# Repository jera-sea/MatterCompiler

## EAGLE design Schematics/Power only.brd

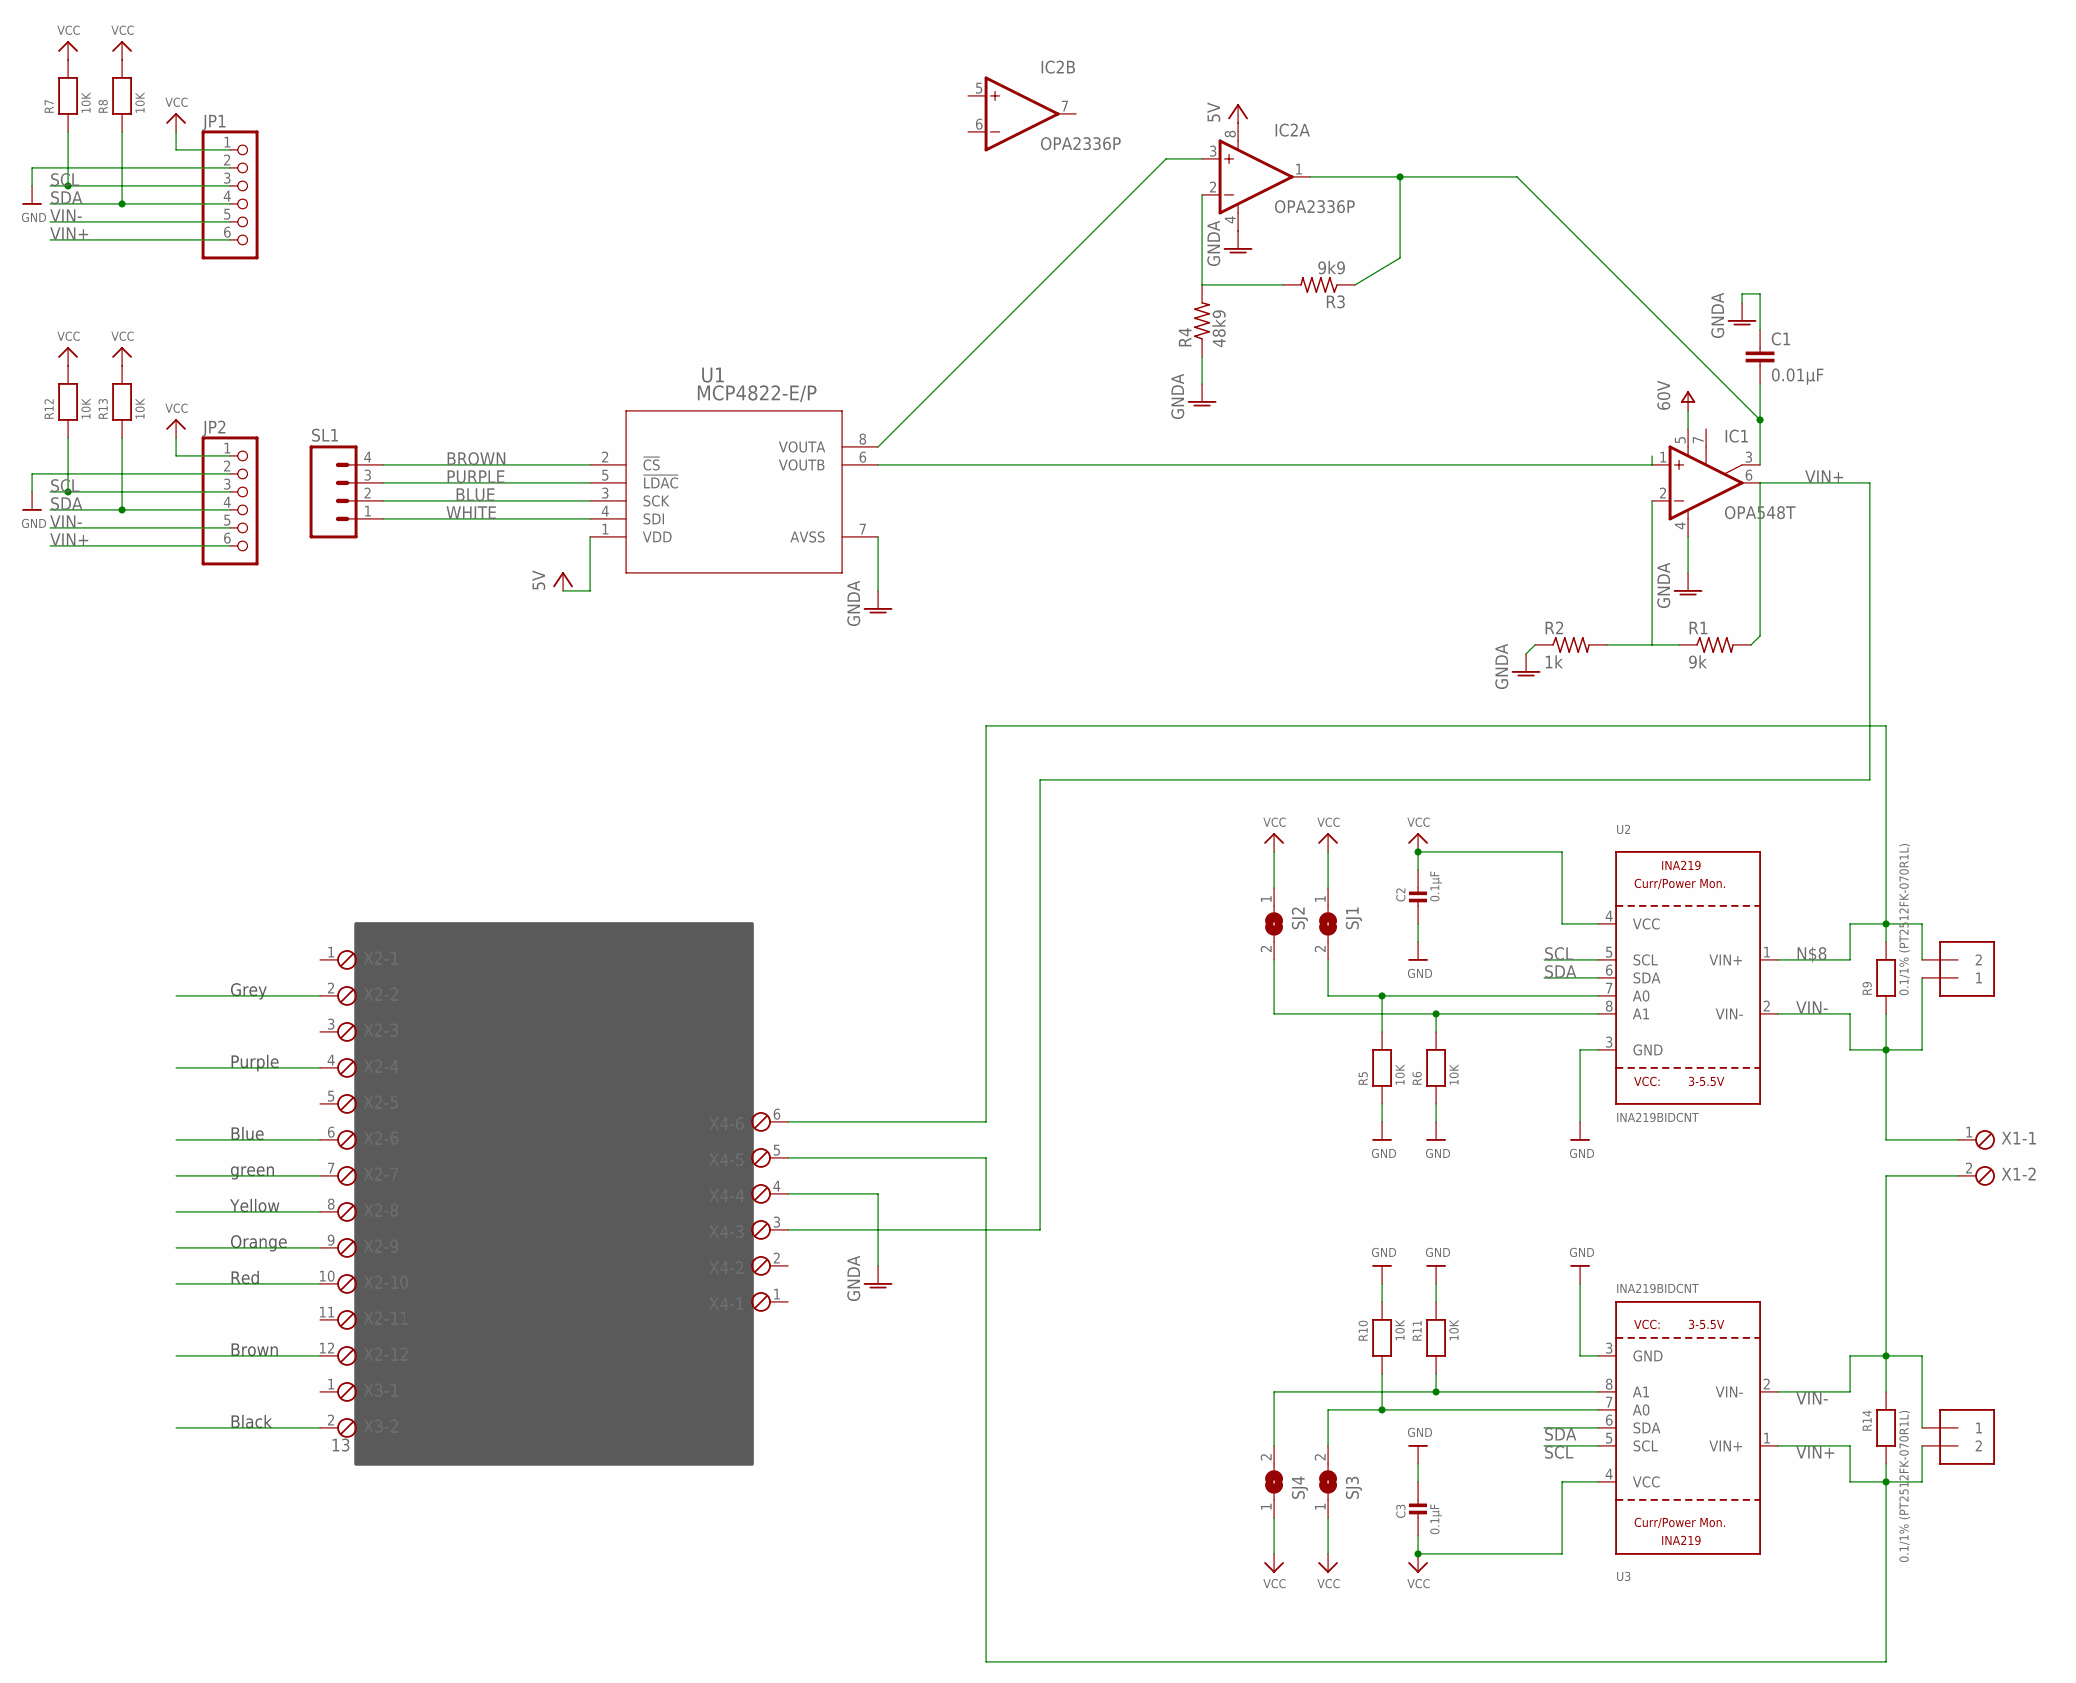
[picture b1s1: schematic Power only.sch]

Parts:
C1: 0.01µF; C5B3
C2, C3: 0.1µF; 0805
IC1: OPA548T; TO220-7
IC2: OPA2336P; DIL08
J1, J2: TERMBLOCK_1X2-3.5MM; 1X2-3.5MM
JP1, JP2: HEADER-1X670MIL; 1X06_ROUND_70
R1: 9k; 0207/7
R2: 1k; 0207/7
R3: 9k9; 0207/7
R4: 48k9; 0207/7
R5, R6, R7, R8, R10, R11, R12, R13: 10K; 0805
R9, R14: 0.1/1% (PT2512FK-070R1L); 2512
SJ1, SJ2, SJ3, SJ4: SOLDERJUMPERREFLOW_NOPASTE; SOLDERJUMPER_REFLOW_NOPASTE
SL1: M04; 04P
U1: MCP4822-E/P; PDIP8_300MC
U2, U3: INA219BIDCNT; SOT23-8
X1: MPT2; 2POL254
X2: MPT12; 12POL254
X3: 13; 2POL254
X4: MPT6; 6POL254

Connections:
BLUE: SL1.2, U1.3 (SCK)
BROWN: SL1.4, U1.2 (!CS)
GND: C2.2, C3.2, JP1.2, JP2.2, R5.1, R6.1, R10.1, R11.1, U2.3 (GND), U3.3 (GND)
GNDA: C1.1, IC1.4 (V-), IC2.4 (V-), R2.1, R4.1, U1.7 (AVSS), X4.4
unnamed: C1.2, IC1.3 (ILIM), IC2.1 (OUT), R3.1
unnamed: IC2.3 (+IN), U1.8 (VOUTA)
unnamed: IC1.2 (-IN), R1.1, R2.2
unnamed: R6.2, SJ2.2, U2.8 (A1)
unnamed: IC2.2 (-IN), R3.2, R4.2
unnamed: R5.2, SJ1.2, U2.7 (A0)
unnamed: J1.2, R9.2, U2.1 (VIN+), X4.6
unnamed: R11.2, SJ4.2, U3.8 (A1)
unnamed: R10.2, SJ3.2, U3.7 (A0)
PURPLE: SL1.3, U1.5 (!LDAC)
SCL: JP1.3, JP2.3, R7.1, R12.1, U2.5 (SCL), U3.5 (SCL)
SDA: JP1.4, JP2.4, R8.1, R13.1, U2.6 (SDA), U3.6 (SDA)
V+: IC1.5 (V+)
VCC: C2.1, C3.1, IC2.8 (V+), JP1.1, JP2.1, R7.2, R8.2, R12.2, R13.2, SJ1.1, SJ2.1, SJ3.1, SJ4.1, U1.1 (VDD), U2.4 (VCC), U3.4 (VCC)
VIN+: IC1.6 (OUT), J2.2, JP1.6, JP2.6, R1.2, R14.2, U3.1 (VIN+), X4.3, X4.5
VIN-: J1.1, J2.1, JP1.5, JP2.5, R9.1, R14.1, U2.2 (VIN-), U3.2 (VIN-), X1.1, X1.2
WHITE: SL1.1, U1.4 (SDI)

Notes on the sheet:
M2PWM
M2DIR
!M2FLT
M1PWM
M1DIR
!M1SLP
!M1FLT
!M2SLP
GND
M1A
M2B
VIN
M2A
Grey
Purple
Blue
green
Yellow
Orange
Red
Brown
Black

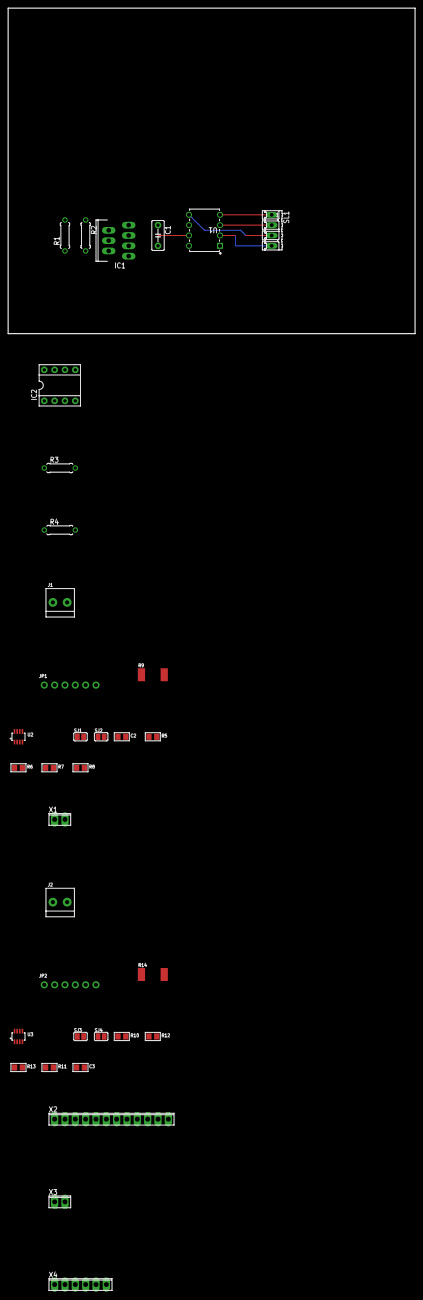
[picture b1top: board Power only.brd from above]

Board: 2 copper layers, 100.0 x 80.0 mm, 35 parts (0 on the bottom side), 20 nets.

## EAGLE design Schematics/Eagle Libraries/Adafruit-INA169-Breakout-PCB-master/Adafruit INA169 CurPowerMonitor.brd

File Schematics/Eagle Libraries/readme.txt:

**********************************************************
*************  Important Instructions Follow  ************
**********************************************************
 
All files exported to: C:\EMA\ExportFolder\0\180488\Output\Eagle\Eagle\Eagle.xml

To import your new library into Eagle:
1. Start Eagle.
2. In the control panel window, Select File -> New -> Library from the menu.
3. In the blank library window, select File -> Execute Script from the menu.
5. Browse to your newly exported Eagle Script file (".scr" file extension)
6. After opening the file, the script will populate the new library.
7. Use File -> Save (or Save As..) to save the library to the desired location in Eagle native format.

For additional information, please visit this site:
http://www.accelerated-designs.com/help/Eagle_import.html

You may also find this video helpful:
http://youtu.be/5jGuWY-Yy3Q

Ultra Librarian Gold 8.2.139 Process Report

Message - Padstack "RX66Y20D0T" Shape(4) is a CIRCLE with no diameter.
Message - Padstack "RX90Y24D0T" Shape(4) is a CIRCLE with no diameter.
Message - Padstack "RX78Y22D0T" Shape(4) is a CIRCLE with no diameter.

TextStyle count:  25
Padstack count:   3
Pattern count:    3
Symbol count:     1
Component count:  1

Export

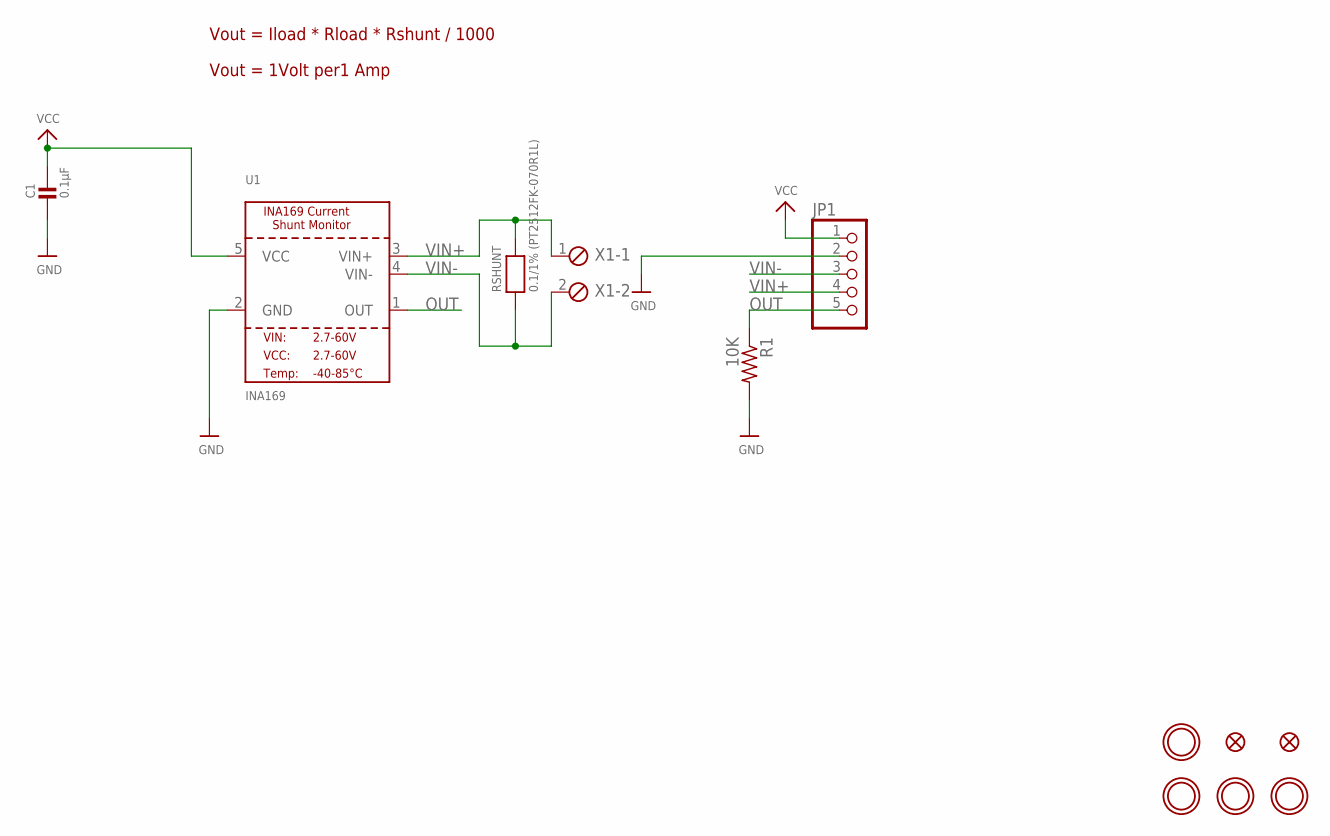
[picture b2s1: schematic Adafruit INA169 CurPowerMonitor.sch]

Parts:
C1: 0.1µF; 0805
FID1, FID2: FIDUCIAL""; FIDUCIAL_1MM
JP1: HEADER-1X570MIL; 1X05_ROUND_70
R1: 10K; 0805-THM
RSHUNT: 0.1/1% (PT2512FK-070R1L); 2512
U1: INA169; SOT23-5
U$7, U$8, U$9, U$10: MOUNTINGHOLE2.5; MOUNTINGHOLE_2.5_PLATED
X1: MPT2; 2POL254

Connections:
GND: C1.2, JP1.2, R1.2, U1.2 (GND)
OUT: JP1.5, R1.1, U1.1 (OUT)
VCC: C1.1, JP1.1, U1.5 (VCC)
VIN+: JP1.4, RSHUNT.2, U1.3 (VIN+), X1.1
VIN-: JP1.3, RSHUNT.1, U1.4 (VIN-), X1.2

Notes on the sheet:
Vout = Iload * Rload * Rshunt / 1000
Vout = 1Volt per1 Amp

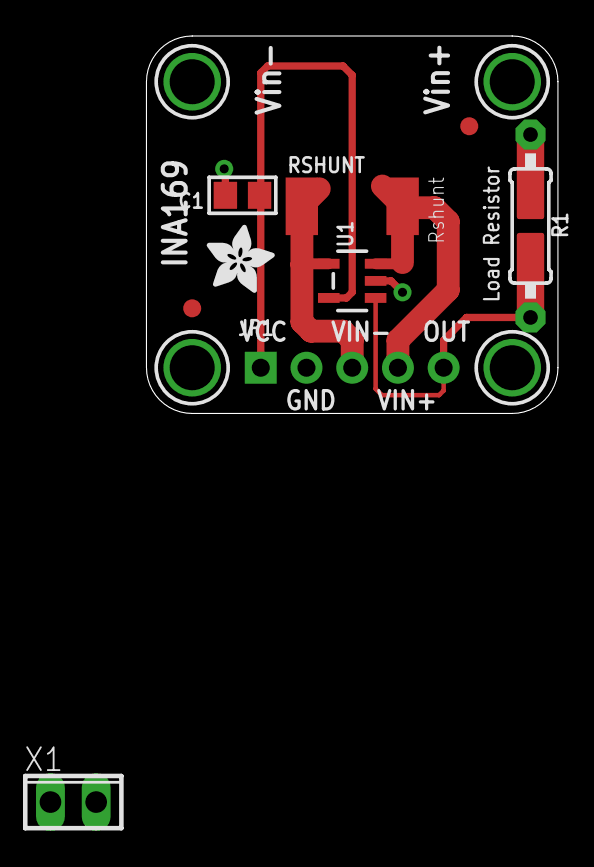
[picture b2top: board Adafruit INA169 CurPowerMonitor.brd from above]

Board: 2 copper layers, 22.9 x 21.0 mm, 13 parts (0 on the bottom side), 5 nets.

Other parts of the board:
U$11: ADAFRUIT_3.5MM

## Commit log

2018-03-25 add arduino code
2018-03-30 added basic code for the variable power supply control
2018-04-02 logging functions basic
    Receive from arduino store in dataframe log to sqlite database
2018-04-03 potentiodynamic sweep
    added arduino functions to perform potentiodynamic sweeps (only up down sweeps implemented).
2018-04-04 waffle
    spent a lot of time adding charge transfer total as a 5 point rolling mean time integral
2018-04-04 hacked it until the loggin worked
    made the serial --> database data stream work
2018-04-07 realtime graph
    added a seperate python script which continuously updates a graph of current vs voltage from the db
2018-04-07 backup
    about to rewrite serial comms
2018-04-07 simpler serial comms
    less logic = more robust serial comms
2018-04-08 added schematics (Half done)
    schematics of power delivery and sensor circuits
2018-04-10 added some pluggery
2018-04-10 Temp sense and H bridge
    plug for temp sensor wiring for H bridge to arduino
2018-04-14 added temp sensor
    Added a ds18b20 temp sensor which updates every 2 seconds (non blocking code)
2018-04-15 pyQT UI started
    Basic pyqt UI testing on RPi
2018-04-15 integrated serial and qt
    Joined the old head.py file with the new main.py which handles UI events (serial reception handles in seperate thread)
2018-04-15 hardware control
    Progress on UI and arduino will now only perform scans, sessions or sensor samples when instructed by the UI
2018-04-16 pyQT controlling arduino
    global serial variable required to allow a seperate thread to read serial while pyqt writes commands
2018-04-16 Voltage Scan with min max and rate
    Rate is affected by a round function requires work (also need to add complex waveforms)
2018-04-17 improved the graph and added error handling
2018-04-17 gtweaks
2018-04-20 ported to RPi and found timing errors
    Bypassed timing errors temporarily using ie_current to pass arduino millis timestamps
2018-04-22 run function
    added unique database names
    added charge accumulation logging
    still required: charge target shutoff (requires relay on output)
2018-04-23 mass transfer limit + current limit
    calibrated the output current limit
    added run function with mass transfer limit (calculated on ideal redox binary NiTi)
2018-04-26 Fixed log message errors
    loggin scan and DC polish cycle working
2018-05-01 more accurate scans
    modded gui
    added opa547 for higher accuracy
2018-05-01 usability changes
    made gui easier to use on touchscreen
    reduced log rate to 5 x per sec
2018-05-08 added tabbed windows
2018-05-16 Added stateMachine
    state tracking for pulse mode
2018-05-22 switched back to high current output
    Low current output was too low for MSA polishing
2018-07-15 Peristaltic Pump
    pump only has speed control
2018-08-20 position sense peristaltic pump
    pulsed control will be possible with analog input
2018-08-27 Added analog input (0-10V)
    not tested
2018-08-30 added analog trigger
    Analog trigger initiates a pulse of fluid at the speed set on the LCD
2018-09-19 Composing Pourbaix Diagrams
    using pymatgen
2018-09-22 generating stability diagrams
2018-11-08 added sem image pixel histogram
    to provide qaulitative measure of surface roughness
2018-11-18 code to control an autolab potentiostat
2018-11-18 1khz aquare wave
2018-11-21 input amplifier
    cleaned the code and added input amplifier transfer function
2018-11-22 untested push
    writing pulse functions
2018-11-23 ready to head to the lab and do some more hacking
    Fwd pulse implemented with increment function. Max freq 760Hz
2018-12-06 FIR voltage limit
    FIR = Forward, interval, reverse pulse pattern
2018-12-08 charge control
    reverse pulse duration is set by charge transferred during forward pulse which observes a voltage limit
2018-12-09 Duty cycle control
    reverse pulse duration is = forward pulse *duty cycle.
    Reverse pulse max current is changed to obtain the required duty cycle.
2019-02-10 Final Version before thesis submission
